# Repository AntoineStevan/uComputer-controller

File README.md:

# A simple game controller for the µ-C1 computer.
This repo and project contain all the files used to create the game controller for the µ-C1 computer.

## Table Of Content.
 - [0  ](https://github.com/AntoineStevan/uComputer-controller/tree/main/#0-prerequisites-toc)  Prerequisites.
 - [1  ](https://github.com/AntoineStevan/uComputer-controller/tree/main/#1-some-images-toc) Some images.
 - [2  ](https://github.com/AntoineStevan/uComputer-controller/tree/main/#2-open-in-kicad-toc)  Open in KiCAD.
 - [2.1](https://github.com/AntoineStevan/uComputer-controller/tree/main/#21-install-kicad-toc) Install KiCAD.
 - [2.2](https://github.com/AntoineStevan/uComputer-controller/tree/main/#22-use-kicad-toc)     Use KiCAD.

## 0. Prerequisites. [[toc](https://github.com/AntoineStevan/uComputer-controller/tree/main/#table-of-content)]
Some schematics and footprints are custom.  
One can find them [here](https://github.com/AntoineStevan/kicad-libraries).

## 1 Some images. [[toc](https://github.com/AntoineStevan/uComputer-controller/tree/main/#table-of-content)]
||
|:--:|
| *preview of the schematics.* |

||
|:--:|
| *preview of the pcb design (front side).* |

||
|:--:|
| *preview of the pcb design (back side).* |

## 2. Open in KiCAD. [[toc](https://github.com/AntoineStevan/uComputer-controller/tree/main/#table-of-content)]
This project has been designed under KiCAD, which is, according to their official website, *an open-source software tool for the creation of electronic schematic diagrams and PCB artwork.*  
All usefull official documentation can be found on the website of the Kicad software [here](https://www.kicad.org/).  
Furthermore, parts have been ordered by [Mouser](https://www.mouser.fr/) and PCBs have been manufactured by [JLCPCB](https://jlcpcb.com/).

### 2.1. Install KiCAD. [[toc](https://github.com/AntoineStevan/uComputer-controller/tree/main/#table-of-content)]
Official KiCAD material can be found [here](https://docs.kicad.org/5.1/en/getting_started_in_kicad/getting_started_in_kicad.html).  
Further specific material for Linux users can be found [here](https://doc.ubuntu-fr.org/kicad).

### 2.2. Use KiCAD. [[toc](https://github.com/AntoineStevan/uComputer-controller/tree/main/#table-of-content)]
The KiCAD team provides plenty of documentation and examples on their official website [here](https://docs.kicad.org/).  
The Internet is also full of great quality tutorials on many topics concerning KiCAD software and schematics/PCB design in general.

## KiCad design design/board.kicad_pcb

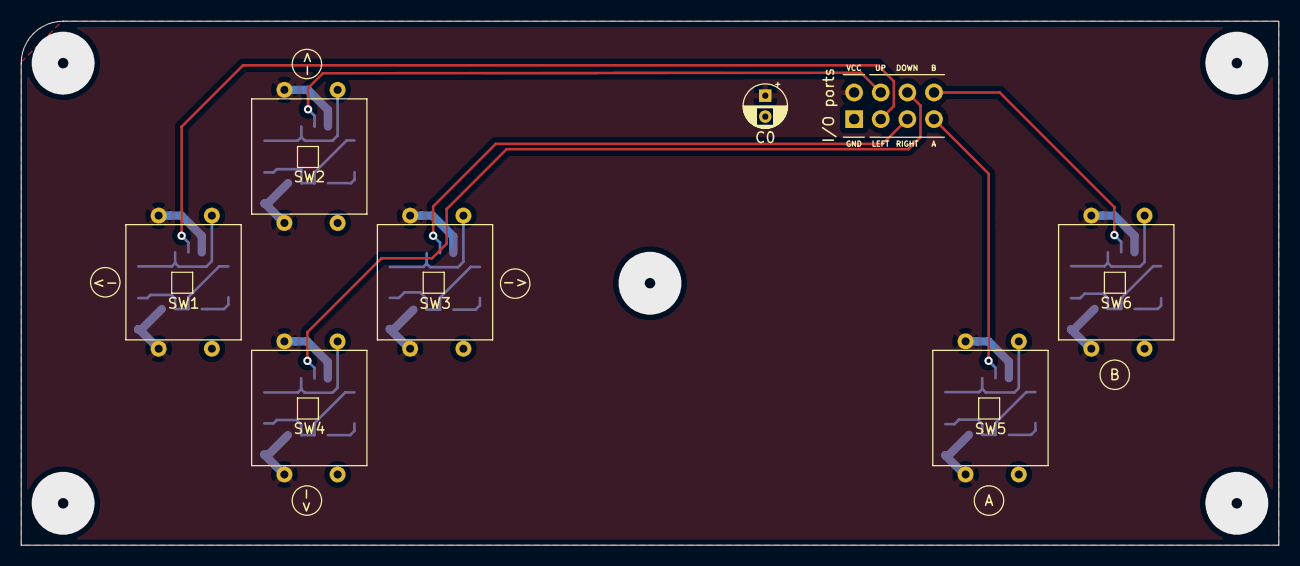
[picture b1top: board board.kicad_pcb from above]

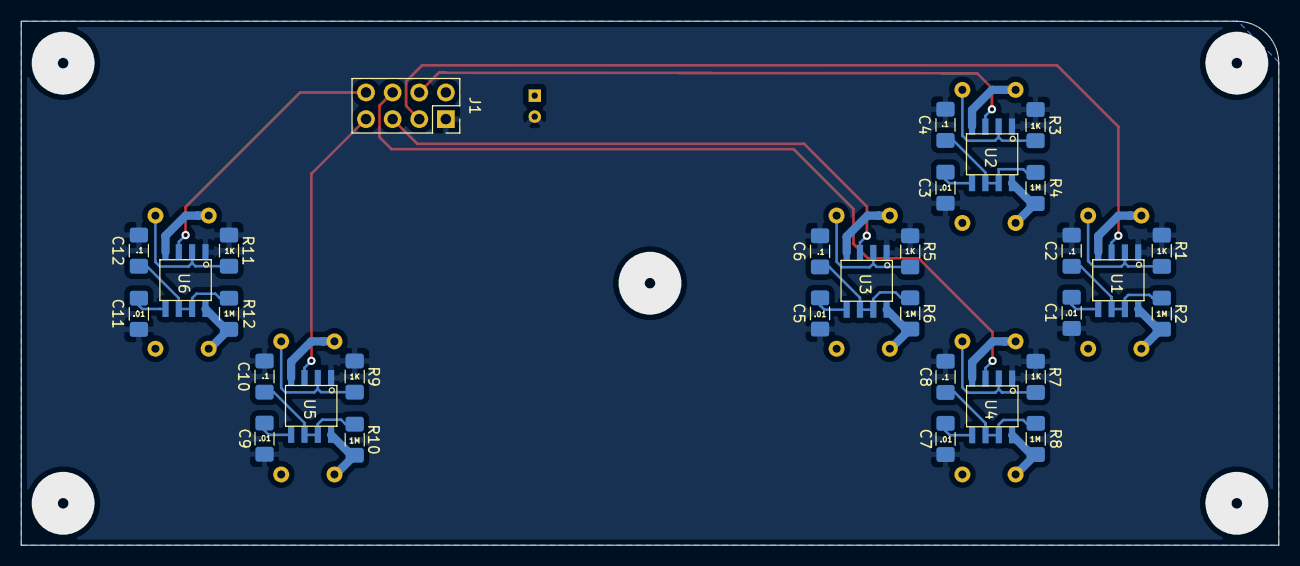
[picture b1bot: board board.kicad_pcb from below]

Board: 2 copper layers, 120.0 x 50.0 mm, 38 parts (31 on the bottom side), 26 nets.

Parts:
C0: CP; CP_Radial_D4.0mm_P2.00mm
C1, C3, C5, C7, C9, C11: 0.01µF; C_1206_3216Metric_Pad1.42x1.75mm_HandSolder
C2, C4, C6, C8, C10, C12: 0.1µF; C_1206_3216Metric_Pad1.42x1.75mm_HandSolder
J1: Conn_02x04_Odd_Even; PinSocket_2x04_P2.54mm_Vertical
R1, R3, R5, R7, R9, R11: 1K; R_1206_3216Metric_Pad1.42x1.75mm_HandSolder
R2, R4, R6, R8, R10, R12: 1M; R_1206_3216Metric_Pad1.42x1.75mm_HandSolder
SW1, SW2, SW3, SW4, SW5, SW6: SW_Push; pushbutton_3x6
U1, U2, U3, U4, U5, U6: LM555; LM555_SOIC-8_p1.27_l1.55_w0.6_W5.4

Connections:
/A_5: C9.2, U5.5
/A_67: C10.2, R10.2, U5.6, U5.7
/A_button: R9.2, SW5.2, U5.2
/A_out: J1.7, U5.3
/B_5: C11.2, U6.5
/B_67: C12.2, R12.2, U6.6, U6.7
/B_button: R11.2, SW6.2, U6.2
/B_out: J1.8, U6.3
/D_5: C7.2, U4.5
/D_67: C8.2, R8.2, U4.6, U4.7
/D_button: R7.2, SW4.2, U4.2
/D_out: J1.6, U4.3
/GND: C0.2, C1.1, C2.1, C3.1, C4.1, C5.1, C6.1, C7.1, C8.1, C9.1, C10.1, C11.1, C12.1, J1.1, R1.1, R3.1, R5.1, R7.1, R9.1, R11.1, U1.1, U2.1, U3.1, U4.1, U5.1, U6.1
/L_5: C1.2, U1.5
/L_67: C2.2, R2.2, U1.6, U1.7
/L_button: R1.2, SW1.2, U1.2
/L_out: J1.3, U1.3
/R_5: C5.2, U3.5
/R_67: C6.2, R6.2, U3.6, U3.7
/R_button: R5.2, SW3.2, U3.2
/R_out: J1.5, U3.3
/U_5: C3.2, U2.5
/U_67: C4.2, R4.2, U2.6, U2.7
/U_button: R3.2, SW2.2, U2.2
/U_out: J1.4, U2.3
/VCC: C0.1, J1.2, R2.1, R4.1, R6.1, R8.1, R10.1, R12.1, SW1.1, SW1.3, SW2.1, SW2.3, SW3.1, SW3.3, SW4.1, SW4.3, SW5.1, SW5.3, SW6.1, SW6.3, U1.4, U1.8, U2.4, U2.8, U3.4, U3.8, U4.4, U4.8, U5.4, U5.8, U6.4, U6.8

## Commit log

2021-09-06 gitignore.
2021-09-06 First schematics.
2021-09-06 Components draft layout + minor changes.
2021-09-07 PCB layout.
2021-09-07 v1 of the controller done.
2021-09-07 Images + README update.
2021-09-07 New decoupling capacitor + mounting holes + image update.
2021-09-07 Correct schematics for the README.md file.
2021-09-07 Path error corrected in README file.
2021-09-07 Minor changes.
2021-09-11 Link to kicad-libraries + futher explainations.
2021-09-11 Correction in the TOC of README.
